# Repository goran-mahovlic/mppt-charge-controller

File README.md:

# MTTP Charge Controller

Adapted from Byte Sized Projects for MEGAphone
Used and released under GPLv3

# mppt charge controller
 
BQ 24650 datasheet can be found here https://www.ti.com/general/docs/suppproductinfo.tsp?distId=10&gotoUrl=https%3A%2F%2Fwww.ti.com%2Flit%2Fgpn%2Fbq24650

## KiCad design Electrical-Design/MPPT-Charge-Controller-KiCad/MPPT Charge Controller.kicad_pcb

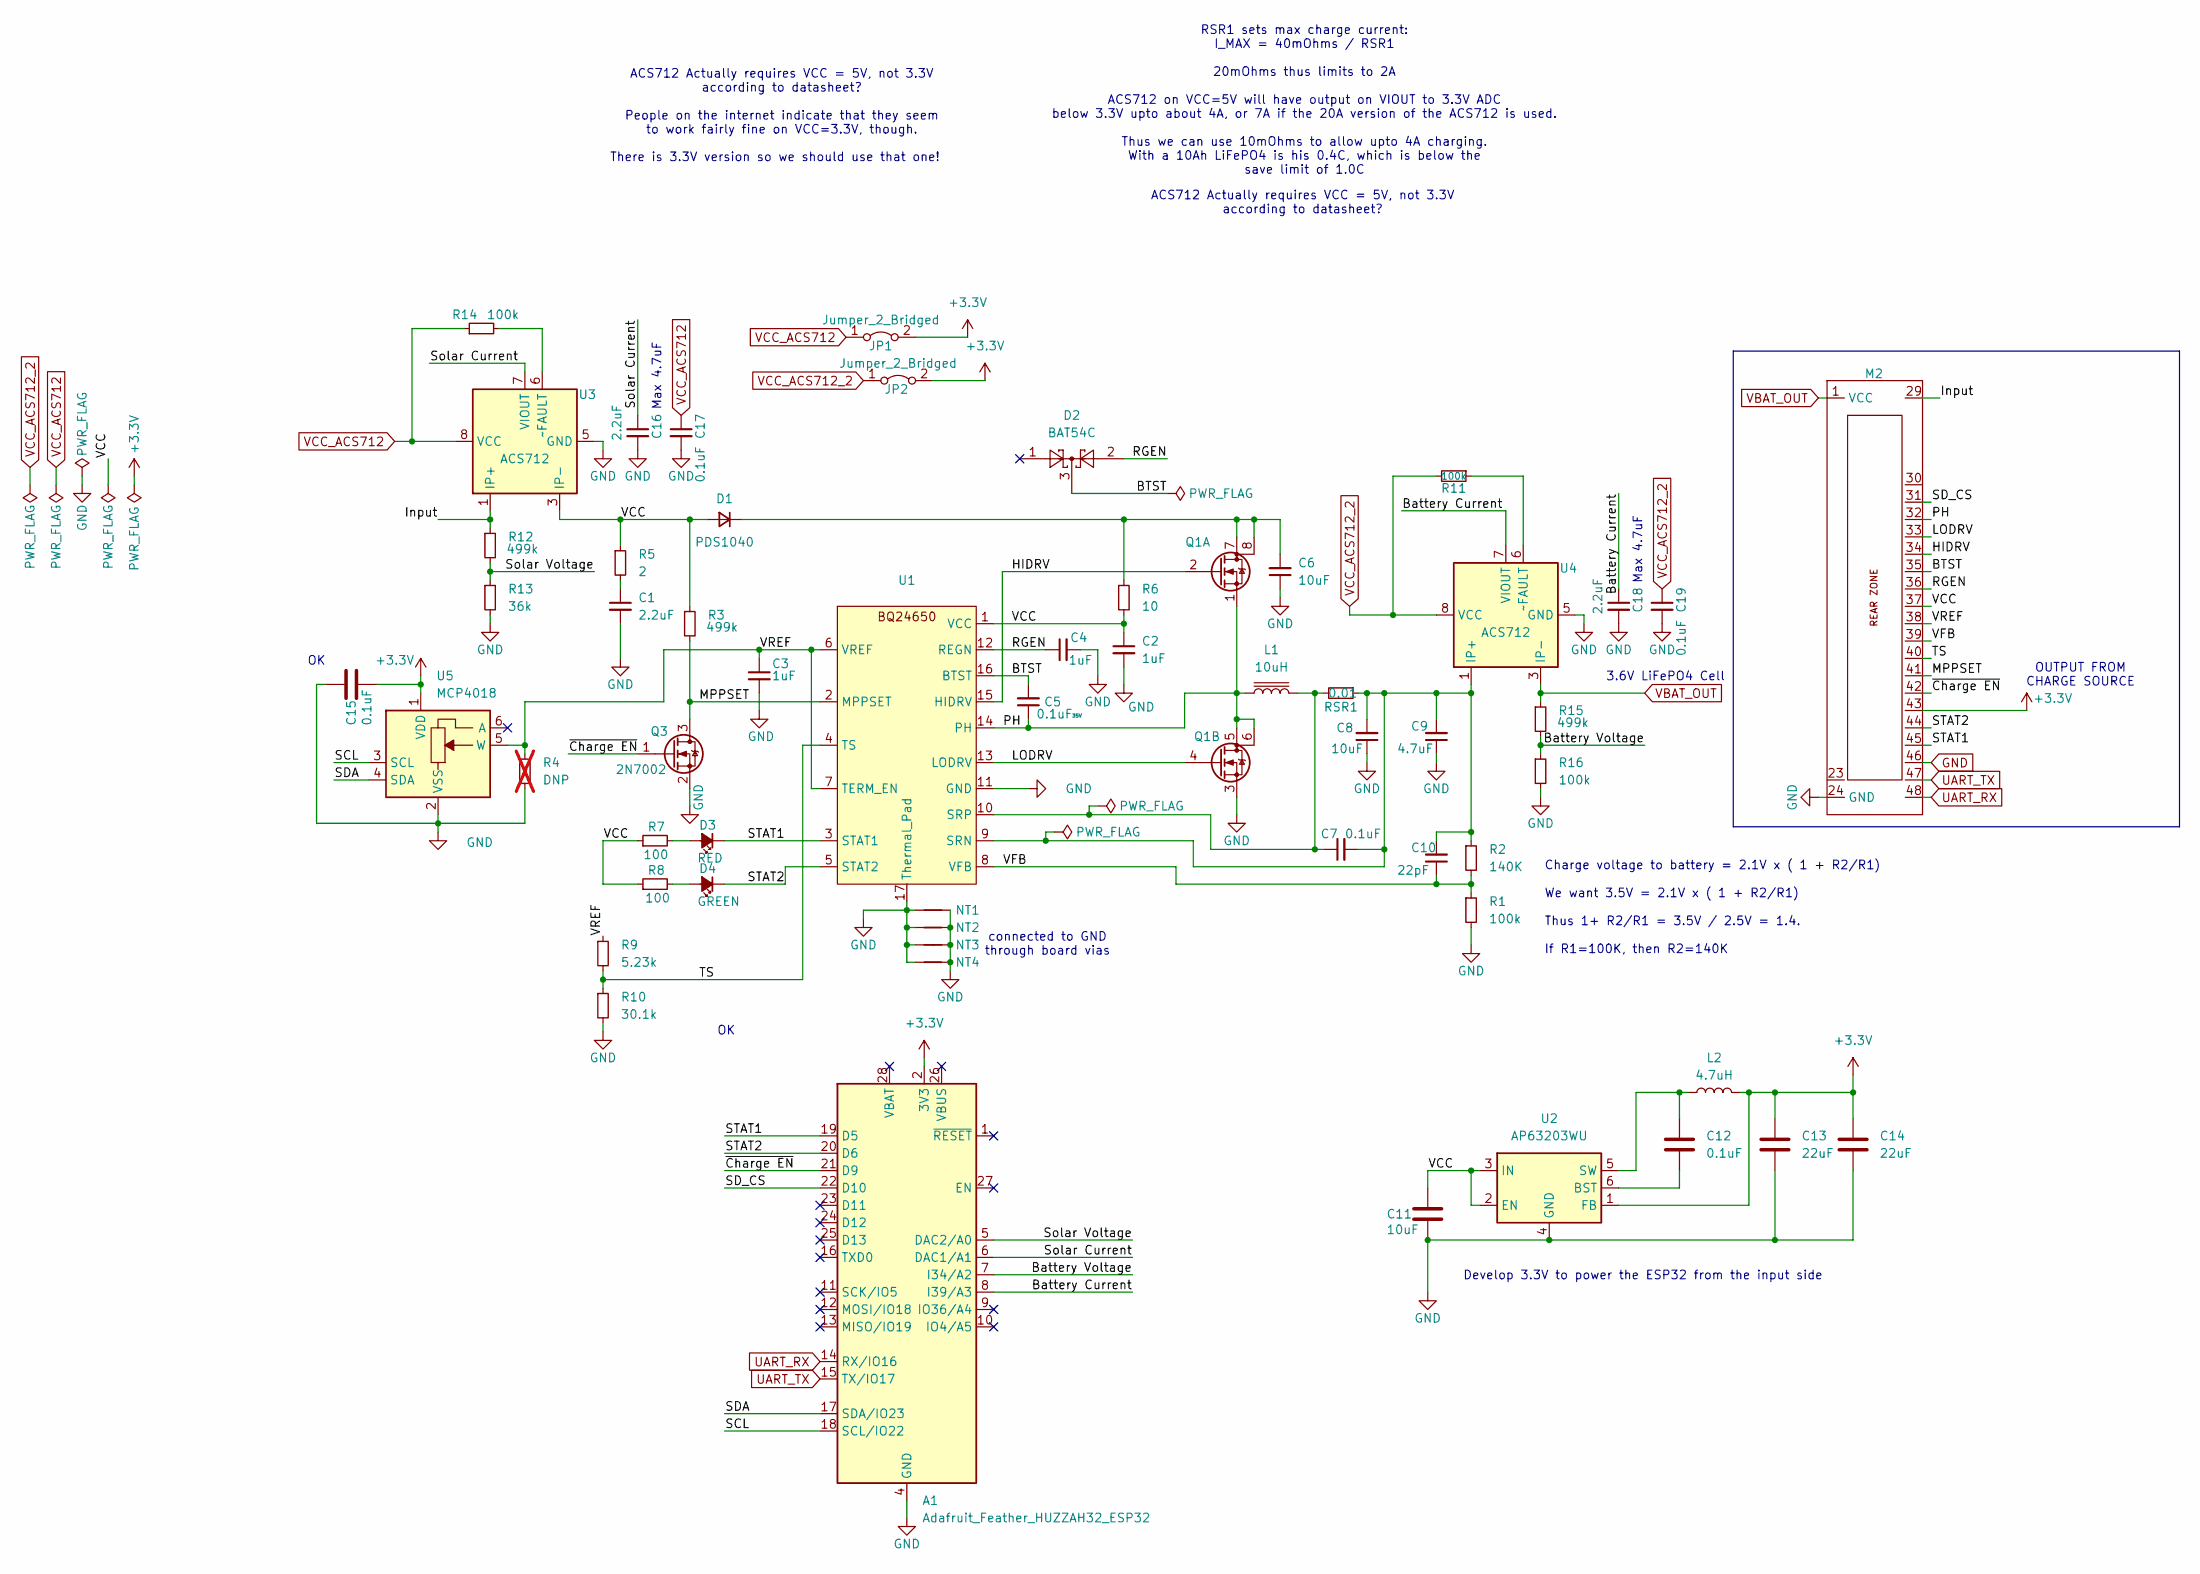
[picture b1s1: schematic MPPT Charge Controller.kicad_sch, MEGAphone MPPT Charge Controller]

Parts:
A1: Adafruit_Feather_HUZZAH32_ESP32; Adafruit_Feather
C1, C16, C18: 2.2uF; C_0603_1608Metric
C2, C3, C4: 1uF; C_0603_1608Metric
C5: 0.1uF; C_0603_1608Metric; Voltage Rating 35V
C6, C8: 10uF; C_1206_3216Metric
C7, C12, C15, C17, C19: 0.1uF; C_0603_1608Metric
C9: 4.7uF; C_0603_1608Metric
C10: 22pF; C_0603_1608Metric
C11: 10uF; C_0603_1608Metric
C13, C14: 22uF; C_0603_1608Metric
D1: PDS1040; D_PowerDI-5
D2: BAT54C; SOT-23
D3: RED; LED_0603_1608Metric
D4: GREEN; LED_0603_1608Metric
JP1, JP2: Jumper_2_Bridged; SolderJumper-2_P1.3mm_Bridged_RoundedPad1.0x1.5mm
L1: 10uH; L_Vishay_6.9x6.5
L2: 4.7uH; L_Vishay_IFSC-1515AH_4x4x1.8mm
M2: MegaCastle2x24-Module-I40.0x56.2-M8000030FFFFF-SPAREPAD
NT1, NT2, NT3, NT4: NetTie-2_SMD_Pad0.5mm
Q1: SI7272DP; PowerPAK_SO-8_Dual
Q3: 2N7002; SOT-23
R1, R11, R14, R16: 100k; R_0603_1608Metric
R2: 140K; R_0603_1608Metric
R3, R12, R15: 499k; R_0603_1608Metric
R4: DNP; R_0603_1608Metric; not fitted
R5: 2; R_2512_6332Metric
R6: 10; R_0603_1608Metric
R7, R8: 100; R_0603_1608Metric
R9: 5.23k; R_0603_1608Metric
R10: 30.1k; R_0603_1608Metric
R13: 36k; R_0603_1608Metric
RSR1: 0.01; R_1206_3216Metric
U1: VQFN-16_EP_3.5x3.5_Pitch0.5mm
U2: AP63203WU; TSOT-23-6
U3, U4: ACS712; SOIC-8_3.9x4.9mm_P1.27mm
U5: MCP4018; SOT-363_SC-70-6

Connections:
+3.3V: A1.2 (3V3), C13.1, C14.1, C15.1, JP1.2 (B), JP2.2 (B), L2.2, M2.43, U2.1 (FB), U5.1 (VDD)
/BTST: C5.2, D2.3, M2.35, U1.16 (BTST)
/Battery Current: A1.8 (I39/A3), C18.1, U4.7 (VIOUT)
/Battery Voltage: A1.7 (I34/A2), R15.2, R16.1
/HIDRV: M2.34, Q1.2 (G), U1.15 (HIDRV)
/Input: M2.29, R12.1, U3.1 (IP+), U3.2 (IP+)
/LODRV: M2.33, Q1.4 (G), U1.13 (LODRV)
/MPPSET: M2.41, Q3.3 (D), R3.2, U1.2 (MPPSET)
/PH: C5.1, L1.1, M2.32, Q1.1 (S), Q1.5 (D), Q1.6 (D), U1.14 (PH)
/RGEN: C4.1, D2.2, M2.36, U1.12 (REGN)
/SCL: A1.18 (SCL/IO22), U5.3 (SCL)
/SDA: A1.17 (SDA/IO23), U5.4 (SDA)
/SD_CS: A1.22 (D10), M2.31
/STAT1: A1.19 (D5), D3.1 (K), M2.45, U1.3 (STAT1)
/STAT2: A1.20 (D6), D4.1 (K), M2.44, U1.5 (STAT2)
/Solar Current: A1.6 (DAC1/A1), C16.1, U3.7 (VIOUT)
/Solar Voltage: A1.5 (DAC2/A0), R12.2, R13.1
/TS: M2.40, R9.2, R10.1, U1.4 (TS)
/VCC: C2.1, C11.2, D1.2 (A), M2.37, R3.1, R5.1, R6.2, R7.1, R8.1, U1.1 (VCC), U2.2 (EN), U2.3 (IN), U3.3 (IP-), U3.4 (IP-)
/VFB: C10.1, M2.39, R1.1, R2.2, U1.8 (VFB)
/VREF: C3.1, M2.38, R4.1, R9.1, U1.6 (VREF), U1.7 (TERM_EN), U5.5 (W)
/~Charge EN: A1.21 (D9), M2.42, Q3.1 (G)
GND: A1.4 (GND), C1.2, C2.2, C3.2, C4.2, C6.1, C8.1, C9.1, C11.1, C13.2, C14.2, C15.2, C16.2, C17.2, C18.2, C19.2, M2.24 (GND), M2.46, NT1.1, NT1.2, NT2.1, NT2.2, NT3.1, NT3.2, NT4.1, NT4.2, Q1.3 (S), Q3.2 (S), R1.2, R4.2, R10.2, R13.2, R16.2, U1.11 (GND), U1.17 (Thermal_Pad), U2.4 (GND), U3.5 (GND), U4.5 (GND), U5.2 (VSS)
unnamed: C1.1, R5.2
unnamed: C6.2, D1.1 (K), Q1.7 (D), Q1.8 (D), R6.1
unnamed: D3.2 (A), R7.2
unnamed: D4.2 (A), R8.2
unnamed: C7.2, C8.2, C9.2, C10.2, R2.1, RSR1.1, U1.9 (SRN), U4.1 (IP+), U4.2 (IP+)
unnamed: C7.1, L1.2, RSR1.2, U1.10 (SRP)
unnamed: C12.2, U2.6 (BST)
unnamed: C12.1, L2.1, U2.5 (SW)
unnamed: R14.2, U3.6 (~FAULT)
unnamed: R11.1, U4.6 (~FAULT)
UART_RX: A1.14 (RX/IO16), M2.48
UART_TX: A1.15 (TX/IO17), M2.47
VBAT_OUT: M2.1 (VCC), R15.1, U4.3 (IP-), U4.4 (IP-)
VCC_ACS712: C17.1, JP1.1 (A), R14.1, U3.8 (VCC)
VCC_ACS712_2: C19.1, JP2.1 (A), R11.2, U4.8 (VCC)

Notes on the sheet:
ACS712 Actually requires VCC = 5V, not 3.3V according to datasheet?
ACS712 Actually requires VCC = 5V, not 3.3V according to datasheet? People on the internet indicate that they seem to work fairly fine on VCC=3.3V, though.
Max 4.7uF
3.6V LiFePO4 Cell
OUTPUT FROM CHARGE SOURCE
Charge voltage to battery = 2.1V x ( 1 + R2/R1) We want 3.5V = 2.1V x ( 1 + R2/R1) Thus 1+ R2/R1 = 3.5V / 2.5V = 1.4. If R1=100K, then R2=140K
RSR1 sets max charge current: I_MAX = 40mOhms / RSR1 20mOhms thus limits to 2A ACS712 on VCC=5V will have output on VIOUT to 3.3V ADC below 3.3V upto about 4A, or 7A if the 20A version of the ACS712 is used. Thus we can use 10mOhms to allow upto 4A charging. With a 10Ah LiFePO4 is his 0.4C, which i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
There is 3.3V version so we should use that one!
connected to GND through board vias
Develop 3.3V to power the ESP32 from the input side

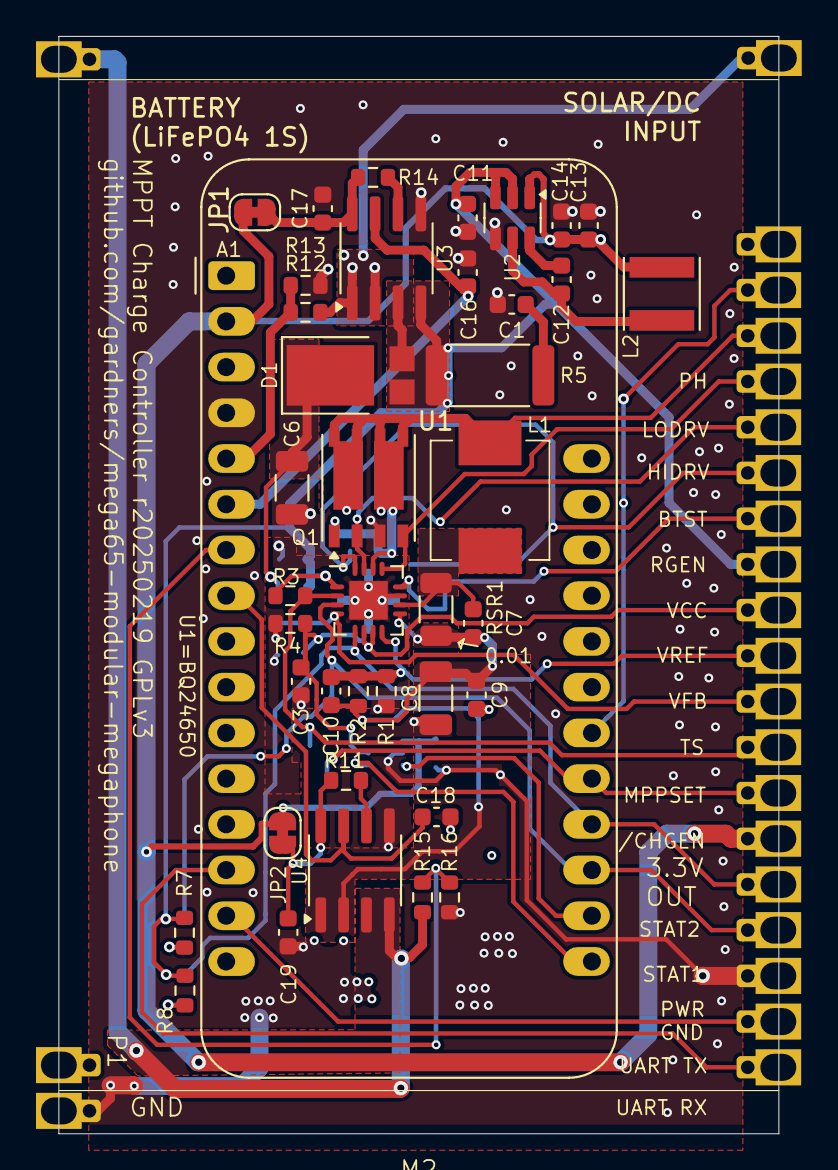
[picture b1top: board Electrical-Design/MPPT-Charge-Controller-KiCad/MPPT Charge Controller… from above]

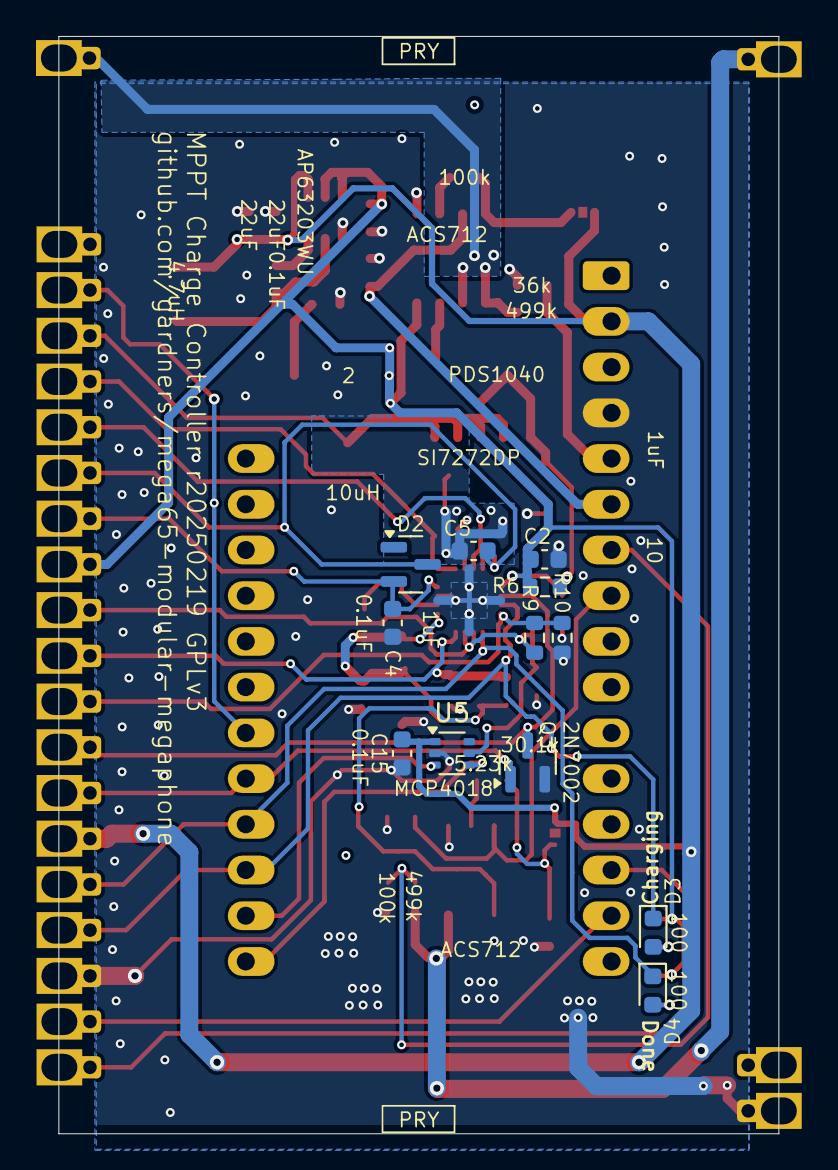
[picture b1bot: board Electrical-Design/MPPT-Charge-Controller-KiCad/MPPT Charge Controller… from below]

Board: 4 copper layers, 40.0 x 61.0 mm, 57 parts (16 on the bottom side), 38 nets.

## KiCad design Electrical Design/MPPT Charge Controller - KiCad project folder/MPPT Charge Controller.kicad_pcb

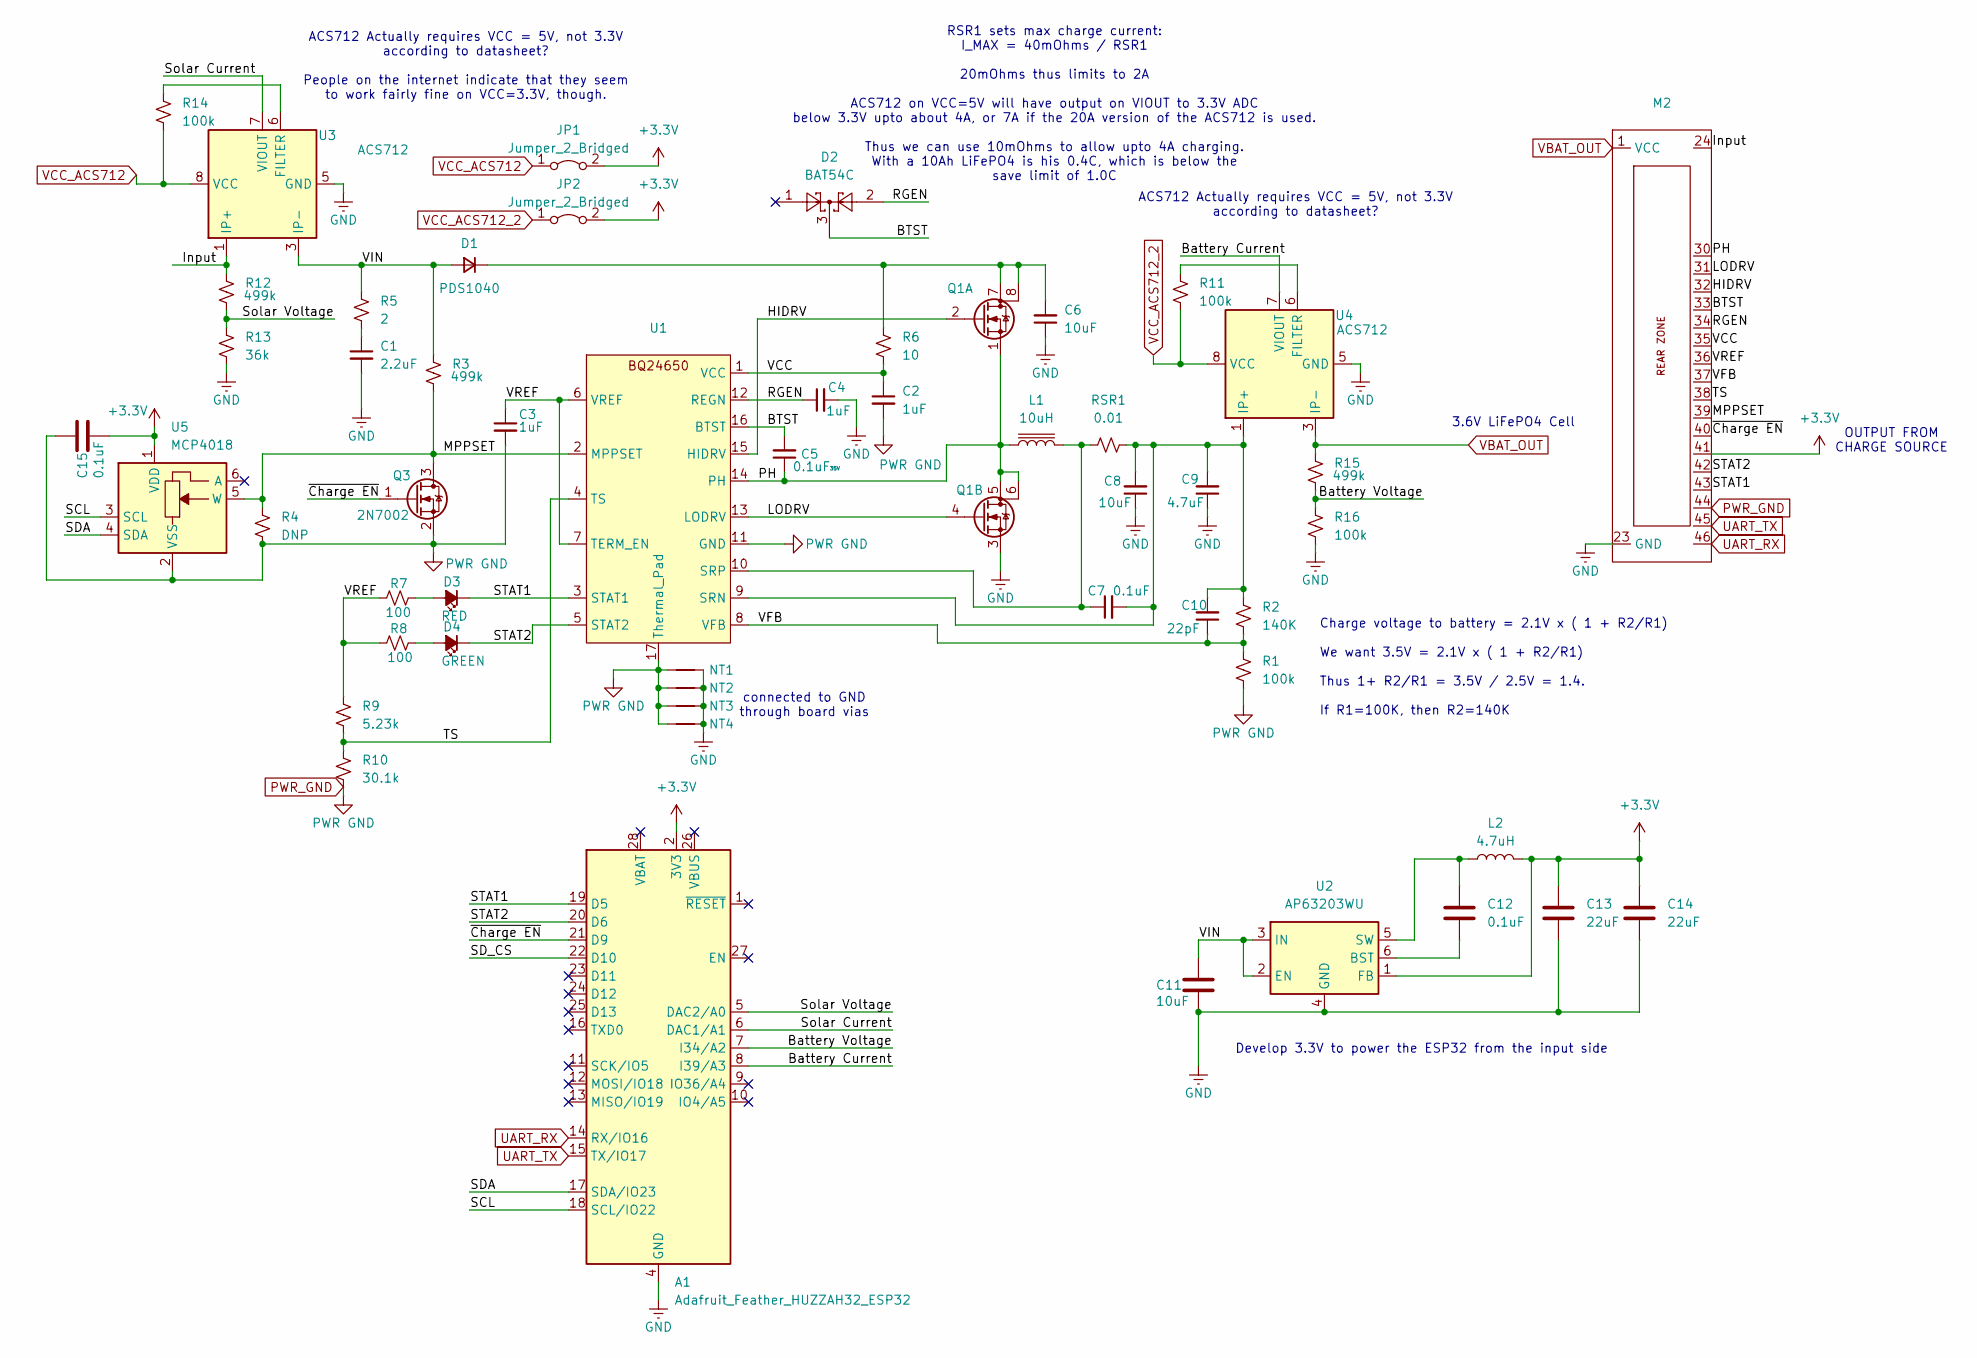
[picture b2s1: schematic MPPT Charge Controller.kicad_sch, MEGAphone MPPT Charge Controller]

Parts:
A1: Adafruit_Feather_HUZZAH32_ESP32; Adafruit_Feather
C1: 2.2uF; C_1210_3225Metric
C2, C3, C4: 1uF; C_0603_1608Metric
C5: 0.1uF; C_0603_1608Metric; Voltage Rating 35V
C6, C8: 10uF; C_1206_3216Metric
C7, C12, C15: 0.1uF; C_0603_1608Metric
C9: 4.7uF; C_0805_2012Metric
C10: 22pF; C_0603_1608Metric
C11: 10uF; C_0603_1608Metric
C13, C14: 22uF; C_0603_1608Metric
D1: PDS1040; D_PowerDI-5
D2: BAT54C; SOT-23
D3: RED; LED_0603_1608Metric
D4: GREEN; LED_0603_1608Metric
JP1, JP2: Jumper_2_Bridged; SolderJumper-2_P1.3mm_Bridged_RoundedPad1.0x1.5mm
L1: 10uH; L_Vishay_6.9x6.5
L2: 4.7uH; L_Vishay_IFSC-1515AH_4x4x1.8mm
M2: MegaCastle2x23-Module-I30.0x53.6-M80000307FFFC-PANEL
NT1, NT2, NT3, NT4: NetTie-2_SMD_Pad0.5mm
Q1: SI7272DP; PowerPAK_SO-8_Dual
Q3: 2N7002; SOT-23
R1, R11, R14, R16: 100k; R_0603_1608Metric
R2: 140K; R_0603_1608Metric
R3, R12, R15: 499k; R_0603_1608Metric
R4: DNP; R_0603_1608Metric
R5: 2; R_2512_6332Metric
R6: 10; R_0603_1608Metric
R7, R8: 100; R_0603_1608Metric
R9: 5.23k; R_0603_1608Metric
R10: 30.1k; R_0603_1608Metric
R13: 36k; R_0603_1608Metric
RSR1: 0.01; R_1206_3216Metric
U1: VQFN-16_EP_3.5x3.5_Pitch0.5mm
U2: AP63203WU; TSOT-23-6
U3, U4: ACS712; SOIC-8_3.9x4.9mm_P1.27mm
U5: MCP4018; SOT-363_SC-70-6

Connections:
+3.3V: A1.2 (3V3), C13.1, C14.1, C15.1, JP1.2 (B), JP2.2 (B), L2.2, M2.41, U2.1 (FB), U5.1 (VDD)
/BTST: C5.2, D2.3, M2.33, U1.16 (BTST)
/Battery Current: A1.8 (I39/A3), U4.7 (VIOUT)
/Battery Voltage: A1.7 (I34/A2), R15.2, R16.1
/HIDRV: M2.32, Q1.2 (G), U1.15 (HIDRV)
/Input: M2.24, R12.1, U3.1 (IP+), U3.2 (IP+)
/LODRV: M2.31, Q1.4 (G), U1.13 (LODRV)
/MPPSET: M2.39, Q3.3 (D), R3.2, R4.1, U1.2 (MPPSET), U5.5 (W)
/PH: C5.1, L1.1, M2.30, Q1.1 (S), Q1.5 (D), Q1.6 (D), U1.14 (PH)
/RGEN: C4.1, D2.2, M2.34, U1.12 (REGN)
/SCL: A1.18 (SCL/IO22), U5.3 (SCL)
/SDA: A1.17 (SDA/IO23), U5.4 (SDA)
/SD_CS: A1.22 (D10)
/STAT1: A1.19 (D5), D3.1 (K), M2.43, U1.3 (STAT1)
/STAT2: A1.20 (D6), D4.1 (K), M2.42, U1.5 (STAT2)
/Solar Current: A1.6 (DAC1/A1), U3.7 (VIOUT)
/Solar Voltage: A1.5 (DAC2/A0), R12.2, R13.1
/TS: M2.38, R9.2, R10.1, U1.4 (TS)
/VCC: C2.1, M2.35, R6.2, U1.1 (VCC)
/VFB: C10.1, M2.37, R1.1, R2.2, U1.8 (VFB)
/VIN: C11.2, D1.2 (A), R3.1, R5.1, U2.2 (EN), U2.3 (IN), U3.3 (IP-), U3.4 (IP-)
/VREF: C3.1, M2.36, R7.1, R8.1, R9.1, U1.6 (VREF), U1.7 (TERM_EN)
/~Charge EN: A1.21 (D9), M2.40, Q3.1 (G)
GND: A1.4 (GND), C1.2, C4.2, C6.1, C8.1, C9.1, C11.1, C13.2, C14.2, M2.23 (GND), NT1.2, NT2.2, NT3.2, NT4.2, Q1.3 (S), R13.2, R16.2, U2.4 (GND), U3.5 (GND), U4.5 (GND)
unnamed: C1.1, R5.2
unnamed: C6.2, D1.1 (K), Q1.7 (D), Q1.8 (D), R6.1
unnamed: D3.2 (A), R7.2
unnamed: D4.2 (A), R8.2
unnamed: C7.2, C8.2, C9.2, C10.2, R2.1, RSR1.1, U1.9 (SRN), U4.1 (IP+), U4.2 (IP+)
unnamed: C7.1, L1.2, RSR1.2, U1.10 (SRP)
unnamed: C12.2, U2.6 (BST)
unnamed: C12.1, L2.1, U2.5 (SW)
unnamed: R14.1, U3.6 (FILTER)
unnamed: R11.1, U4.6 (FILTER)
PWR_GND: C2.2, C3.2, C15.2, M2.44, NT1.1, NT2.1, NT3.1, NT4.1, Q3.2 (S), R1.2, R4.2, R10.2, U1.11 (GND), U1.17 (Thermal_Pad), U5.2 (VSS)
UART_RX: A1.14 (RX/IO16), M2.46
UART_TX: A1.15 (TX/IO17), M2.45
VBAT_OUT: M2.1 (VCC), R15.1, U4.3 (IP-), U4.4 (IP-)
VCC_ACS712: JP1.1 (A), R14.2, U3.8 (VCC)
VCC_ACS712_2: JP2.1 (A), R11.2, U4.8 (VCC)

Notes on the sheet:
ACS712 Actually requires VCC = 5V, not 3.3V according to datasheet?
ACS712 Actually requires VCC = 5V, not 3.3V according to datasheet? People on the internet indicate that they seem to work fairly fine on VCC=3.3V, though.
3.6V LiFePO4 Cell
OUTPUT FROM CHARGE SOURCE
Charge voltage to battery = 2.1V x ( 1 + R2/R1) We want 3.5V = 2.1V x ( 1 + R2/R1) Thus 1+ R2/R1 = 3.5V / 2.5V = 1.4. If R1=100K, then R2=140K
RSR1 sets max charge current: I_MAX = 40mOhms / RSR1 20mOhms thus limits to 2A ACS712 on VCC=5V will have output on VIOUT to 3.3V ADC below 3.3V upto about 4A, or 7A if the 20A version of the ACS712 is used. Thus we can use 10mOhms to allow upto 4A charging. With a 10Ah LiFePO4 is his 0.4C, which i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
connected to GND through board vias
Develop 3.3V to power the ESP32 from the input side

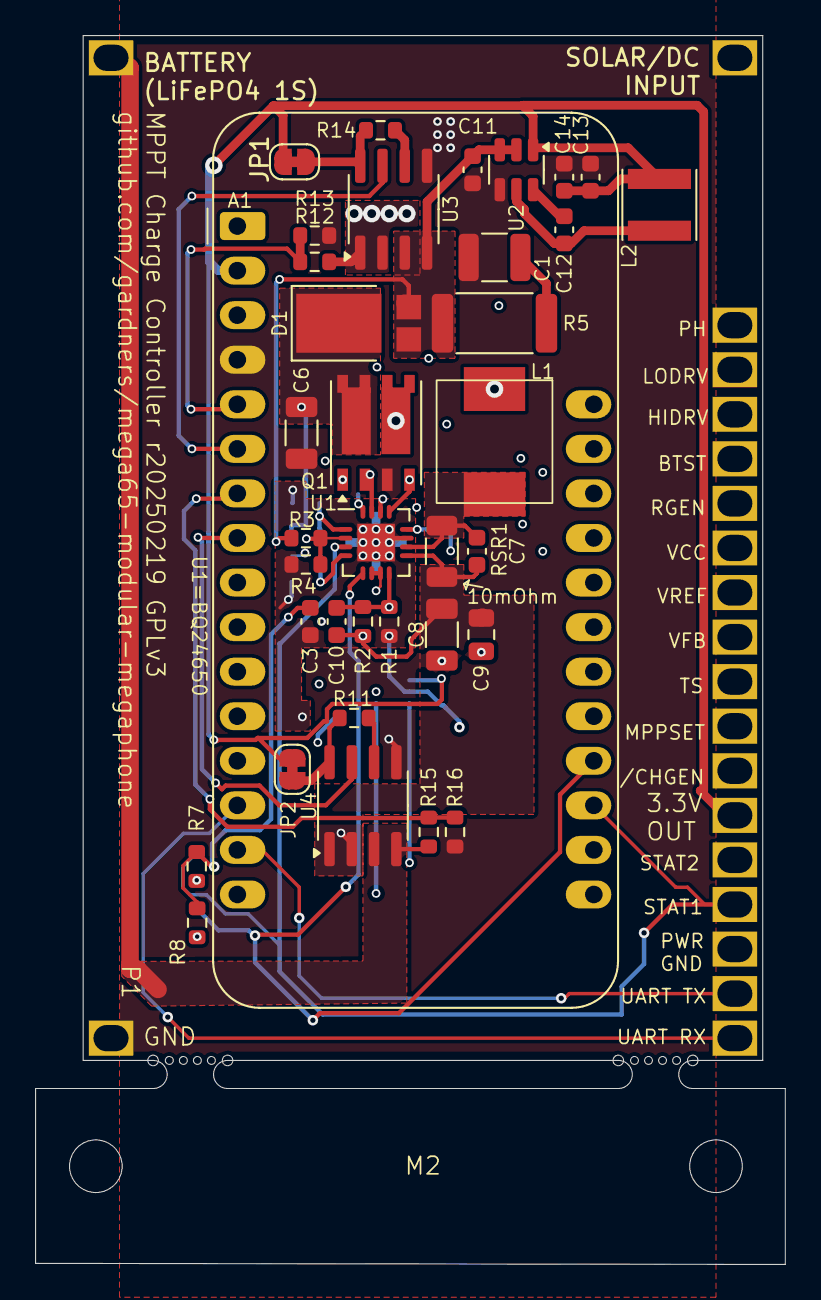
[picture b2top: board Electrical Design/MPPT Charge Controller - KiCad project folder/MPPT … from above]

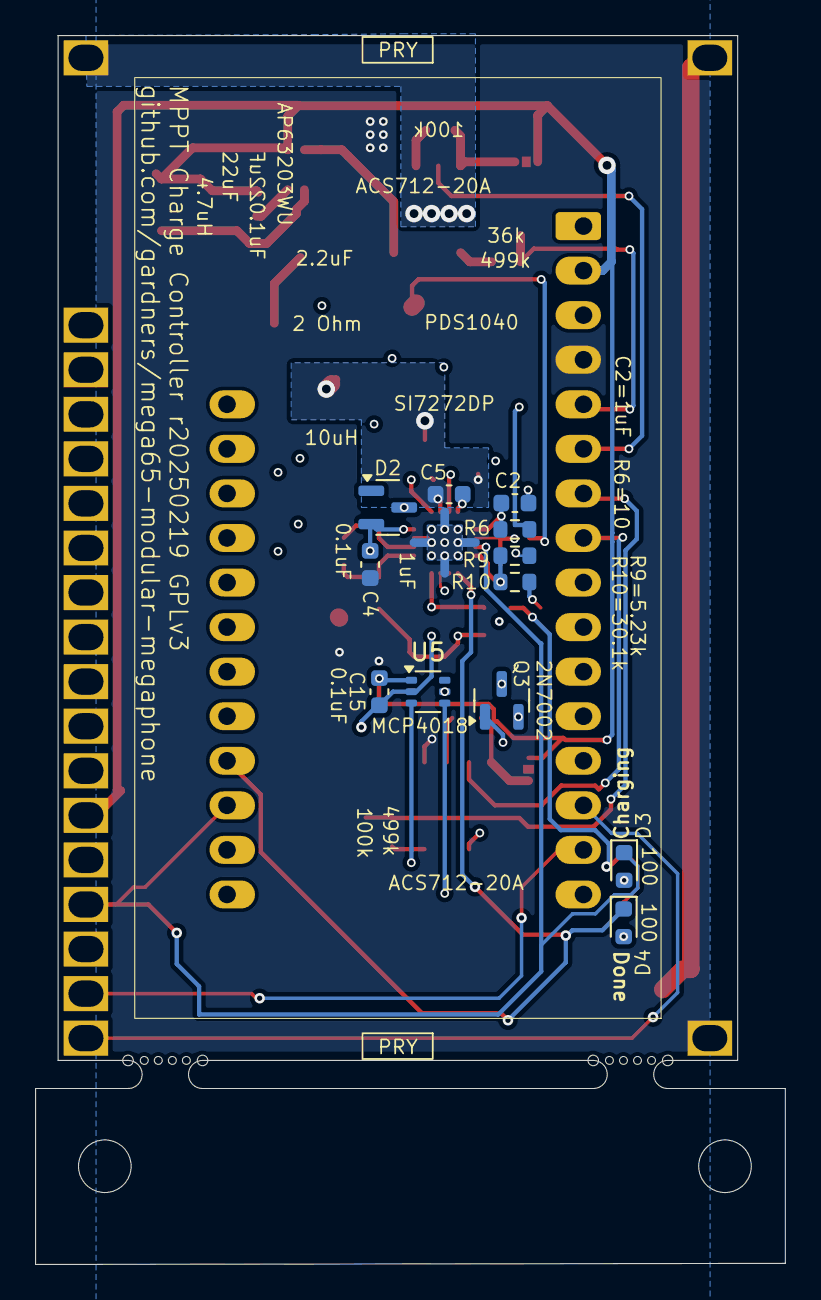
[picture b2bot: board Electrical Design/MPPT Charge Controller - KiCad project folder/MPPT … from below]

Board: 4 copper layers, 42.7 x 70.0 mm, 53 parts (16 on the bottom side), 39 nets.

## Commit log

2025-02-09 update VBAT to 3.5V for single LiFePO4 cell
2025-02-09 add measurement markers for main area of circuit.
2025-02-09 update PCB for 140K R2
2025-02-15 continue to adapt for MEGAphone
2025-02-15 resolve most DRC violations
2025-02-16 add silkscreen for all component values
2025-02-16 update module information on PCB
2025-02-17 switch to panelised footprint
2025-02-17 finish panelising
2025-02-19 prepare for initial fabrication: No castellation, single instance
2025-08-11 Updating shematics - renaming
2025-08-11 Update schematics - delete tracks - 4 layer boards have only 2 signal layers
2025-08-13 Routing, adding schematics
2025-08-13 Routing

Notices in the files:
Electrical Design/MPPT Charge Controller - KiCad project folder/MPPT Charge Controller.kicad_pcb:
${TITLE} r20250219 GPLv3
